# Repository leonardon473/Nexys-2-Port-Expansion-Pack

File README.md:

# Nexys2 Port Expansion Pack
## Expansion Pack for 3 ports with Leds and Dip Switch to the Nexys 2
### This PCB wotks with 3.3v like Nexys 2

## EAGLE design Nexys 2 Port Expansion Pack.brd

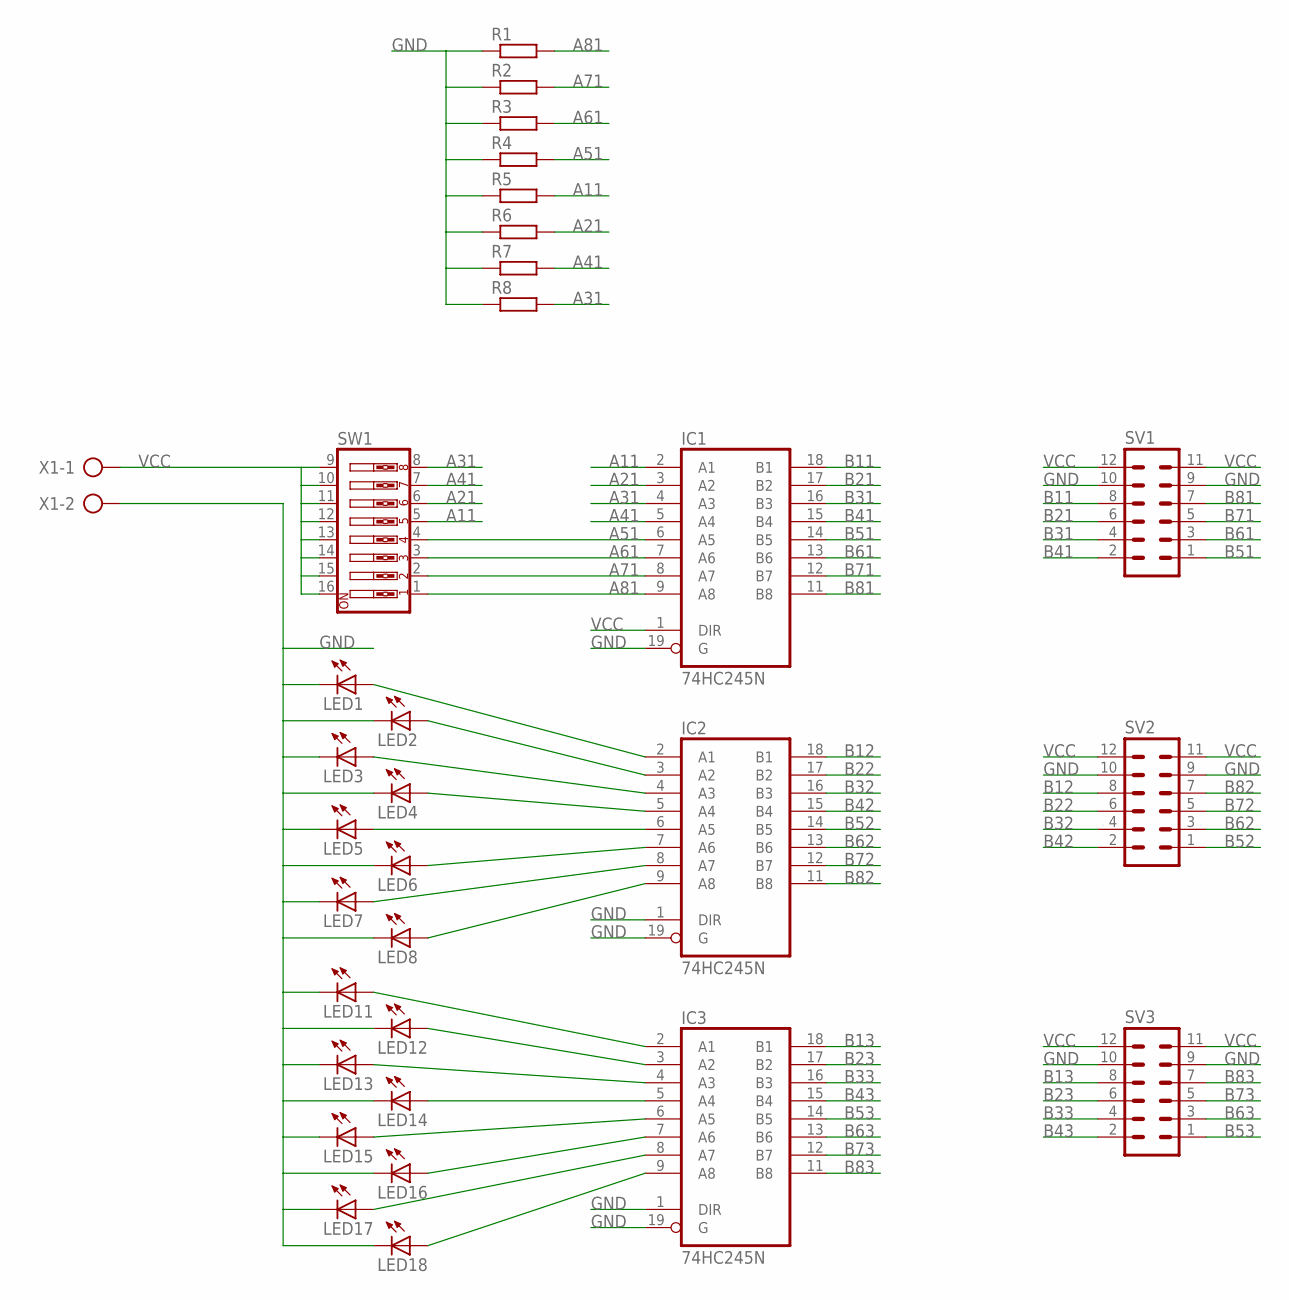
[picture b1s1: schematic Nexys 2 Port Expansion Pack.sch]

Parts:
IC1, IC2, IC3: 74HC245N; DIL20
LED1, LED2, LED3, LED4, LED5, LED6, LED7, LED8, LED11, LED12, LED13, LED14, LED15, LED16, LED17, LED18: LED3MM
R1, R2, R3, R4, R5, R6, R7, R8: R-EU_0207/15; 0207/15
SV1, SV2, SV3: MA06-2
SW1: SW_DIP-8; EDG-08
X1: AK500/2

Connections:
A11: IC1.2 (A1), R5.2, SW1.5
A21: IC1.3 (A2), R6.2, SW1.6
A31: IC1.4 (A3), R8.2, SW1.8
A41: IC1.5 (A4), R7.2, SW1.7
A51: IC1.6 (A5), R4.2, SW1.4
A61: IC1.7 (A6), R3.2, SW1.3
A71: IC1.8 (A7), R2.2, SW1.2
A81: IC1.9 (A8), R1.2, SW1.1
B11: IC1.18 (B1), SV1.8
B12: IC2.18 (B1), SV2.8
B13: IC3.18 (B1), SV3.8
B21: IC1.17 (B2), SV1.6
B22: IC2.17 (B2), SV2.6
B23: IC3.17 (B2), SV3.6
B31: IC1.16 (B3), SV1.4
B32: IC2.16 (B3), SV2.4
B33: IC3.16 (B3), SV3.4
B41: IC1.15 (B4), SV1.2
B42: IC2.15 (B4), SV2.2
B43: IC3.15 (B4), SV3.2
B51: IC1.14 (B5), SV1.1
B52: IC2.14 (B5), SV2.1
B53: IC3.14 (B5), SV3.1
B61: IC1.13 (B6), SV1.3
B62: IC2.13 (B6), SV2.3
B63: IC3.13 (B6), SV3.3
B71: IC1.12 (B7), SV1.5
B72: IC2.12 (B7), SV2.5
B73: IC3.12 (B7), SV3.5
B81: IC1.11 (B8), SV1.7
B82: IC2.11 (B8), SV2.7
B83: IC3.11 (B8), SV3.7
GND: IC1.10 (GND), IC1.19 (G), IC2.1 (DIR), IC2.10 (GND), IC2.19 (G), IC3.1 (DIR), IC3.10 (GND), IC3.19 (G), LED1.K (C), LED2.K (C), LED3.K (C), LED4.K (C), LED5.K (C), LED6.K (C), LED7.K (C), LED8.K (C), LED11.K (C), LED12.K (C), LED13.K (C), LED14.K (C), LED15.K (C), LED16.K (C), LED17.K (C), LED18.K (C), R1.1, R2.1, R3.1, R4.1, R5.1, R6.1, R7.1, R8.1, SV1.9, SV1.10, SV2.9, SV2.10, SV3.9, SV3.10, X1.2
unnamed: IC2.2 (A1), LED1.A
unnamed: IC2.3 (A2), LED2.A
unnamed: IC3.2 (A1), LED11.A
unnamed: IC2.4 (A3), LED3.A
unnamed: IC2.5 (A4), LED4.A
unnamed: IC2.6 (A5), LED5.A
unnamed: IC2.7 (A6), LED6.A
unnamed: IC2.8 (A7), LED7.A
unnamed: IC2.9 (A8), LED8.A
unnamed: IC3.3 (A2), LED12.A
unnamed: IC3.4 (A3), LED13.A
unnamed: IC3.5 (A4), LED14.A
unnamed: IC3.6 (A5), LED15.A
unnamed: IC3.7 (A6), LED16.A
unnamed: IC3.8 (A7), LED17.A
unnamed: IC3.9 (A8), LED18.A
VCC: IC1.1 (DIR), IC1.20 (VCC), IC2.20 (VCC), IC3.20 (VCC), SV1.11, SV1.12, SV2.11, SV2.12, SV3.11, SV3.12, SW1.9, SW1.10, SW1.11, SW1.12, SW1.13, SW1.14, SW1.15, SW1.16, X1.1

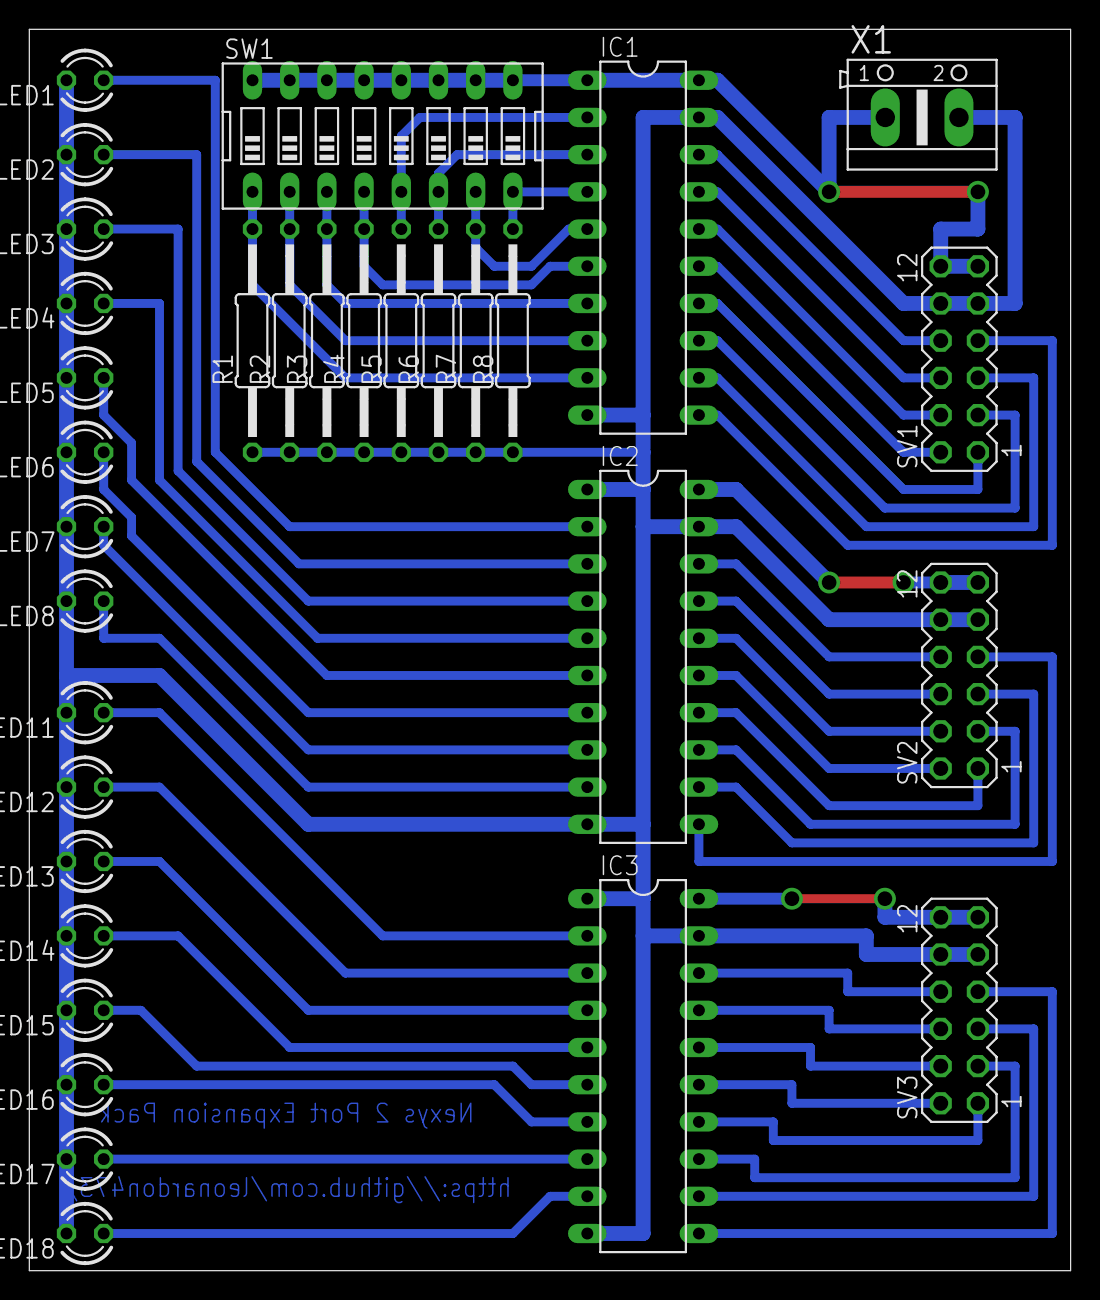
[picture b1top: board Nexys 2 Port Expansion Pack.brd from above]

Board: 2 copper layers, 71.1 x 84.8 mm, 32 parts (0 on the bottom side), 50 nets.

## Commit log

2017-08-24 Add the files to the repo
2017-08-26 Add resistence to the dipswitch
2017-08-26 Add description
2017-08-26 Add voltaje work to 3.3v
2017-08-31 Separate the tracks
2017-08-31 I separated the tracks
